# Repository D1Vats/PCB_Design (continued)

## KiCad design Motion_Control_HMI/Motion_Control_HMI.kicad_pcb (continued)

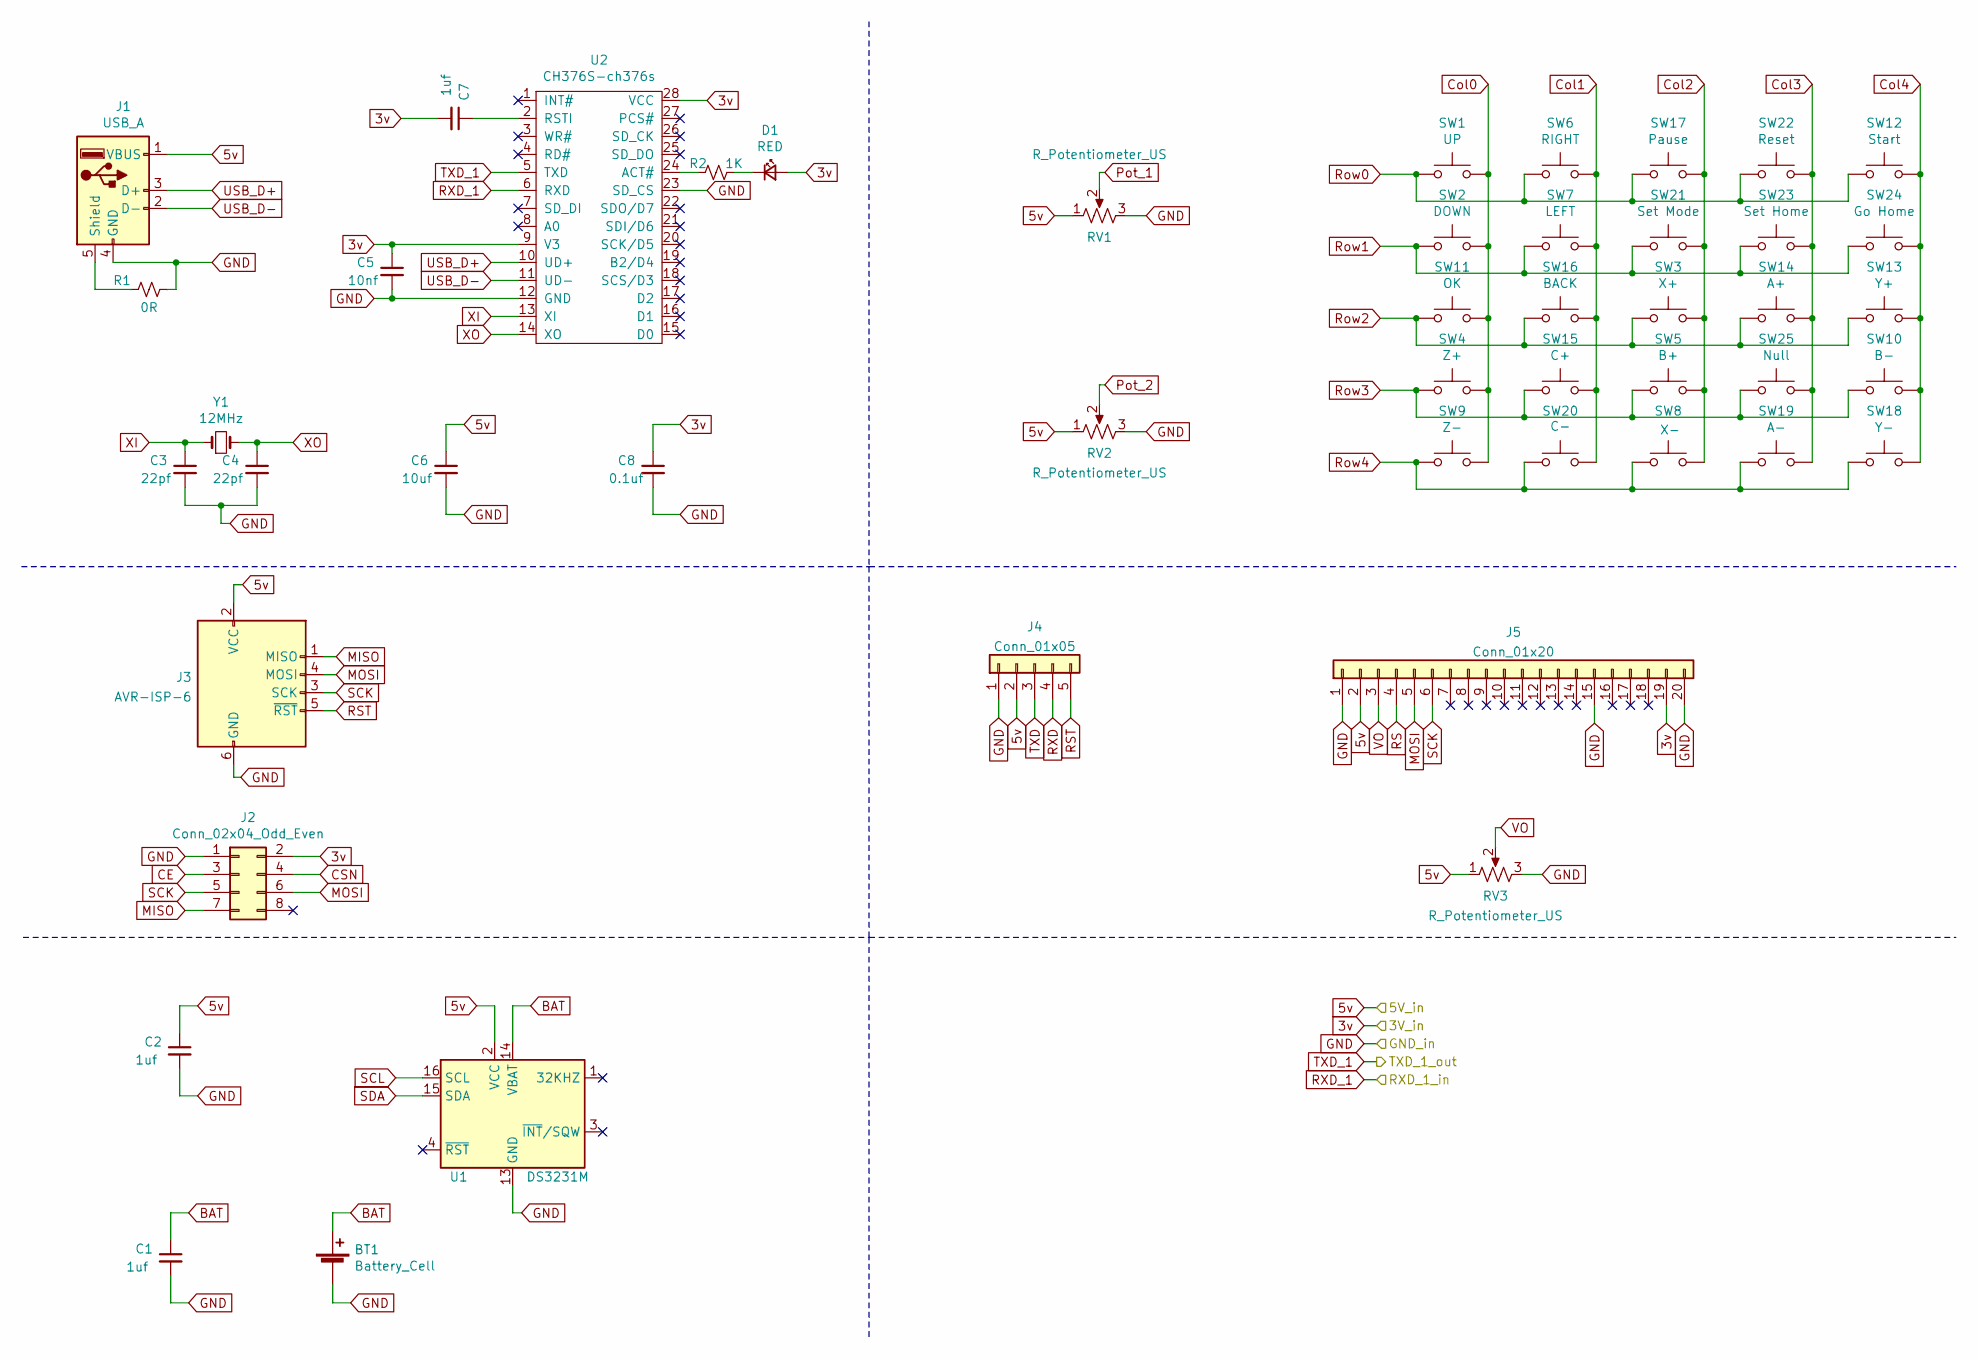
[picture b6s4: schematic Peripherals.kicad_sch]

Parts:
BT1: Battery_Cell; BatteryHolder_Keystone_104_1x23mm
C1, C2, C7: 1uf; C_0805_2012Metric
C3, C4: 22pf; C_0805_2012Metric
C5: 10nf; C_0805_2012Metric
C6: 10uf; C_0805_2012Metric
C8: 0.1uf; C_0805_2012Metric
D1: RED; LED_0805_2012Metric
J1: USB_A; USB_A_Molex_67643_Horizontal
J2: Conn_02x04_Odd_Even; PinSocket_2x04_P2.54mm_Vertical
J3: AVR-ISP-6; PinHeader_2x03_P2.54mm_Vertical
J4: Conn_01x05; PinHeader_1x05_P2.54mm_Vertical
J5: Conn_01x20; PinHeader_1x20_P2.54mm_Vertical
R1: 0R; R_0805_2012Metric
R2: 1K; R_0805_2012Metric
RV1, RV2: R_Potentiometer_US; JST_EH_B3B-EH-A_1x03_P2.50mm_Vertical
RV3: R_Potentiometer_US; Potentiometer_ACP_CA9-H3,8_Horizontal
SW1: UP; Key_Dome
SW2: DOWN; Key_Dome
SW3: X+; Key_Dome
SW4: Z+; Key_Dome
SW5: B+; Key_Dome
SW6: RIGHT; Key_Dome
SW7: LEFT; Key_Dome
SW8: X-; Key_Dome
SW9: Z-; Key_Dome
SW10: B-; Key_Dome
SW11: OK; Key_Dome
SW12: Start; Key_Dome
SW13: Y+; Key_Dome
SW14: A+; Key_Dome
SW15: C+; Key_Dome
SW16: BACK; Key_Dome
SW17: Pause; Key_Dome
SW18: Y-; Key_Dome
SW19: A-; Key_Dome
SW20: C-; Key_Dome
SW21: Set Mode; Key_Dome
SW22: Reset; Key_Dome
SW23: Set Home; Key_Dome
SW24: Go Home; Key_Dome
SW25: Null; Key_Dome
U1: DS3231M; SOIC-16W_7.5x10.3mm_P1.27mm
U2: CH376S-ch376s; SOIC-28W_7.5x17.9mm_P1.27mm
Y1: 12MHz; Crystal_HC49-4H_Vertical

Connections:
3.3V_OUT: C5.1, C7.2, C8.1, D1.2 (A), J2.2, J5.19, U2.9 (V3), U2.28 (VCC); also elsewhere on the board
5v: C2.1, C6.1, J1.1 (VBUS), J3.2 (VCC), J4.2, J5.2, RV1.1, RV2.1, RV3.1, U1.2 (VCC); also elsewhere on the board
BAT: BT1.1 (+), C1.1, U1.14 (VBAT)
CE: J2.3; also elsewhere on the board
CSN: J2.4; also elsewhere on the board
Col0: SW1.2, SW2.2, SW4.2, SW9.2, SW11.2; also elsewhere on the board
Col1: SW6.2, SW7.2, SW15.2, SW16.2, SW20.2; also elsewhere on the board
Col2: SW3.2, SW5.2, SW8.2, SW17.2, SW21.2; also elsewhere on the board
Col3: SW14.2, SW19.2, SW22.2, SW23.2, SW25.2; also elsewhere on the board
Col4: SW10.2, SW12.2, SW13.2, SW18.2, SW24.2; also elsewhere on the board
GND: BT1.2 (-), C1.2, C2.2, C3.2, C4.2, C5.2, C6.2, C8.2, J1.4 (GND), J2.1, J3.6 (GND), J4.1, J5.1, J5.15, J5.20, R1.1, RV1.3, RV2.3, RV3.3, U1.5 (GND), U1.6 (GND), U1.7 (GND), U1.8 (GND), U1.9 (GND), U1.10 (GND), U1.11 (GND), U1.12 (GND), U1.13 (GND), U2.12 (GND), U2.23 (SD_CS); also elsewhere on the board
LV_TXD_1: U2.6 (RXD); also elsewhere on the board
MISO: J2.7, J3.1 (MISO); also elsewhere on the board
MOSI: J2.6, J3.4 (MOSI), J5.5; also elsewhere on the board
unnamed: C7.1, U2.2 (RSTI)
unnamed: D1.1 (K), R2.1
unnamed: J1.5 (Shield), R1.2
unnamed: R2.2, U2.24 (ACT#)
Pot_1: RV1.2; also elsewhere on the board
Pot_2: RV2.2; also elsewhere on the board
RS: J5.4; also elsewhere on the board
RST: J3.5 (~RST), J4.5; also elsewhere on the board
RXD: J4.4; also elsewhere on the board
Row0: SW1.1, SW6.1, SW12.1, SW17.1, SW22.1; also elsewhere on the board
Row1: SW2.1, SW7.1, SW21.1, SW23.1, SW24.1; also elsewhere on the board
Row2: SW3.1, SW11.1, SW13.1, SW14.1, SW16.1; also elsewhere on the board
Row3: SW4.1, SW5.1, SW10.1, SW15.1, SW25.1; also elsewhere on the board
Row4: SW8.1, SW9.1, SW18.1, SW19.1, SW20.1; also elsewhere on the board
SCK: J2.5, J3.3 (SCK), J5.6; also elsewhere on the board
SCL: U1.16 (SCL); also elsewhere on the board
SDA: U1.15 (SDA); also elsewhere on the board
TXD: J4.3; also elsewhere on the board
TXD_1: U2.5 (TXD); also elsewhere on the board
USB_D+: J1.3 (D+), U2.10 (UD+)
USB_D-: J1.2 (D-), U2.11 (UD-)
VO: J5.3, RV3.2
XI: C3.1, U2.13 (XI), Y1.1
XO: C4.1, U2.14 (XO), Y1.2

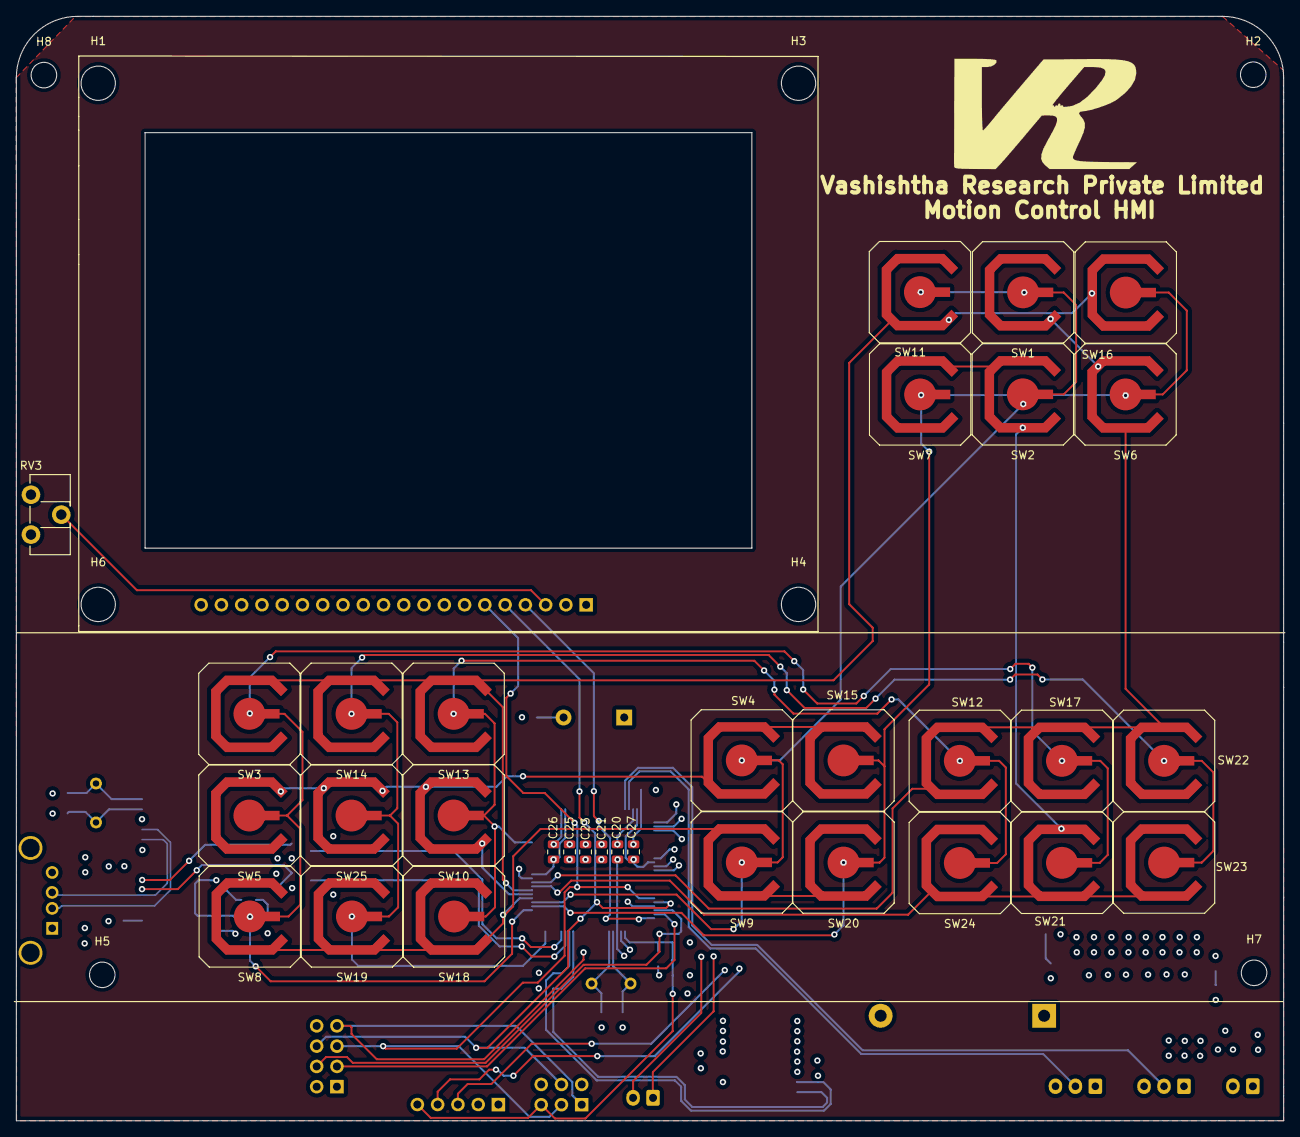
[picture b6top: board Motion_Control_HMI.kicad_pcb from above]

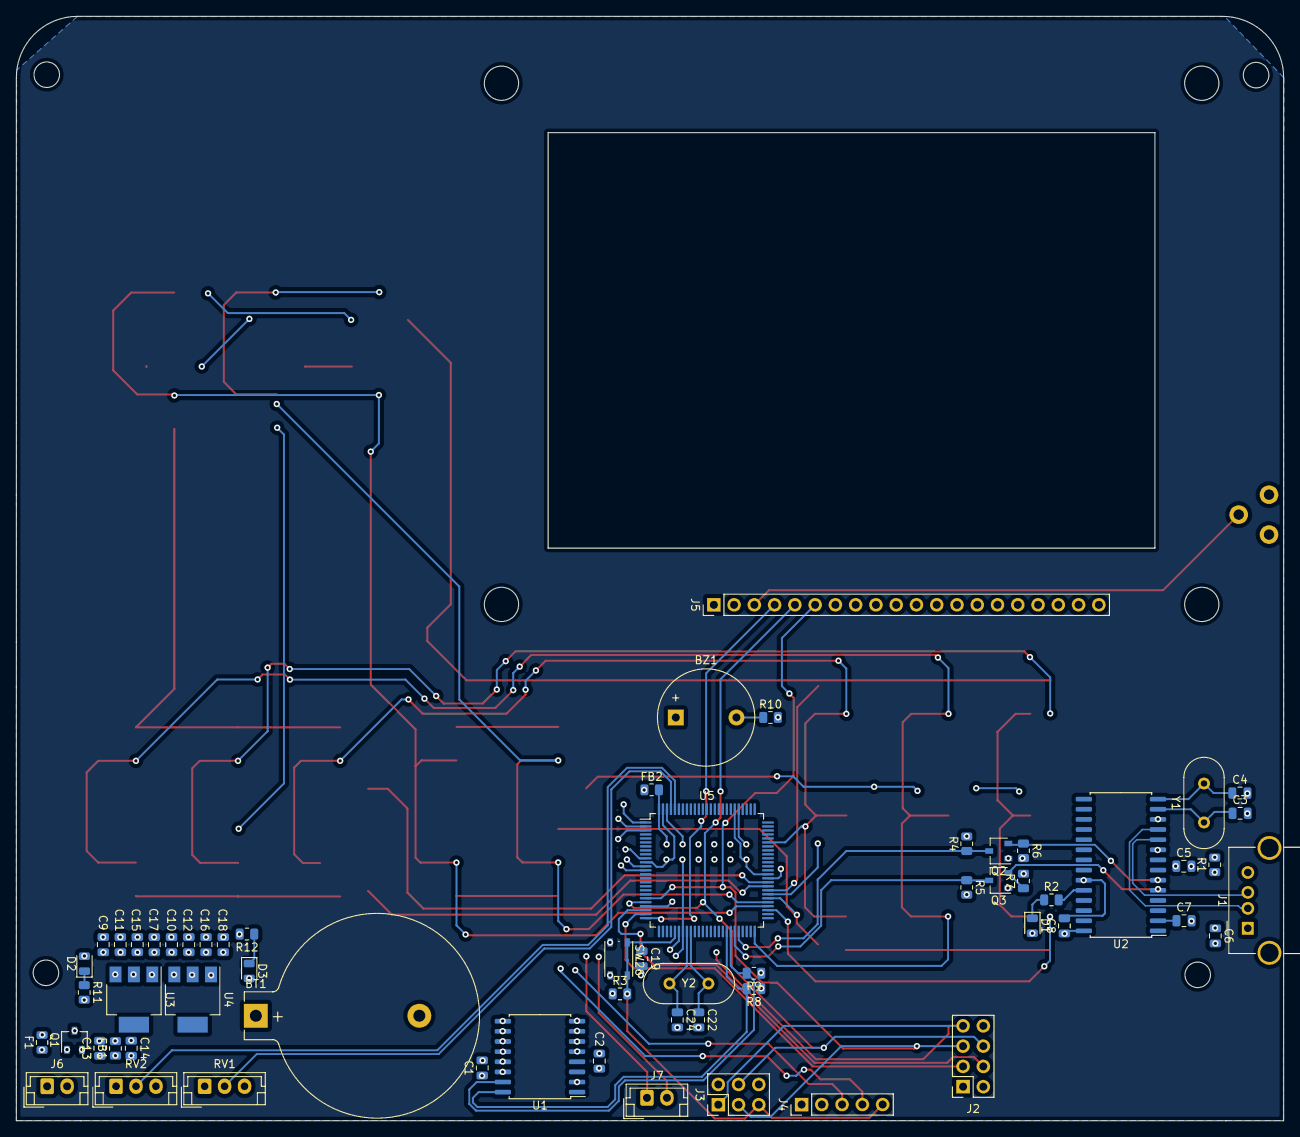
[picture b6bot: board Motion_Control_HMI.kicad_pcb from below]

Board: 4 copper layers, 158.9 x 138.4 mm, 101 parts (61 on the bottom side), 54 nets.

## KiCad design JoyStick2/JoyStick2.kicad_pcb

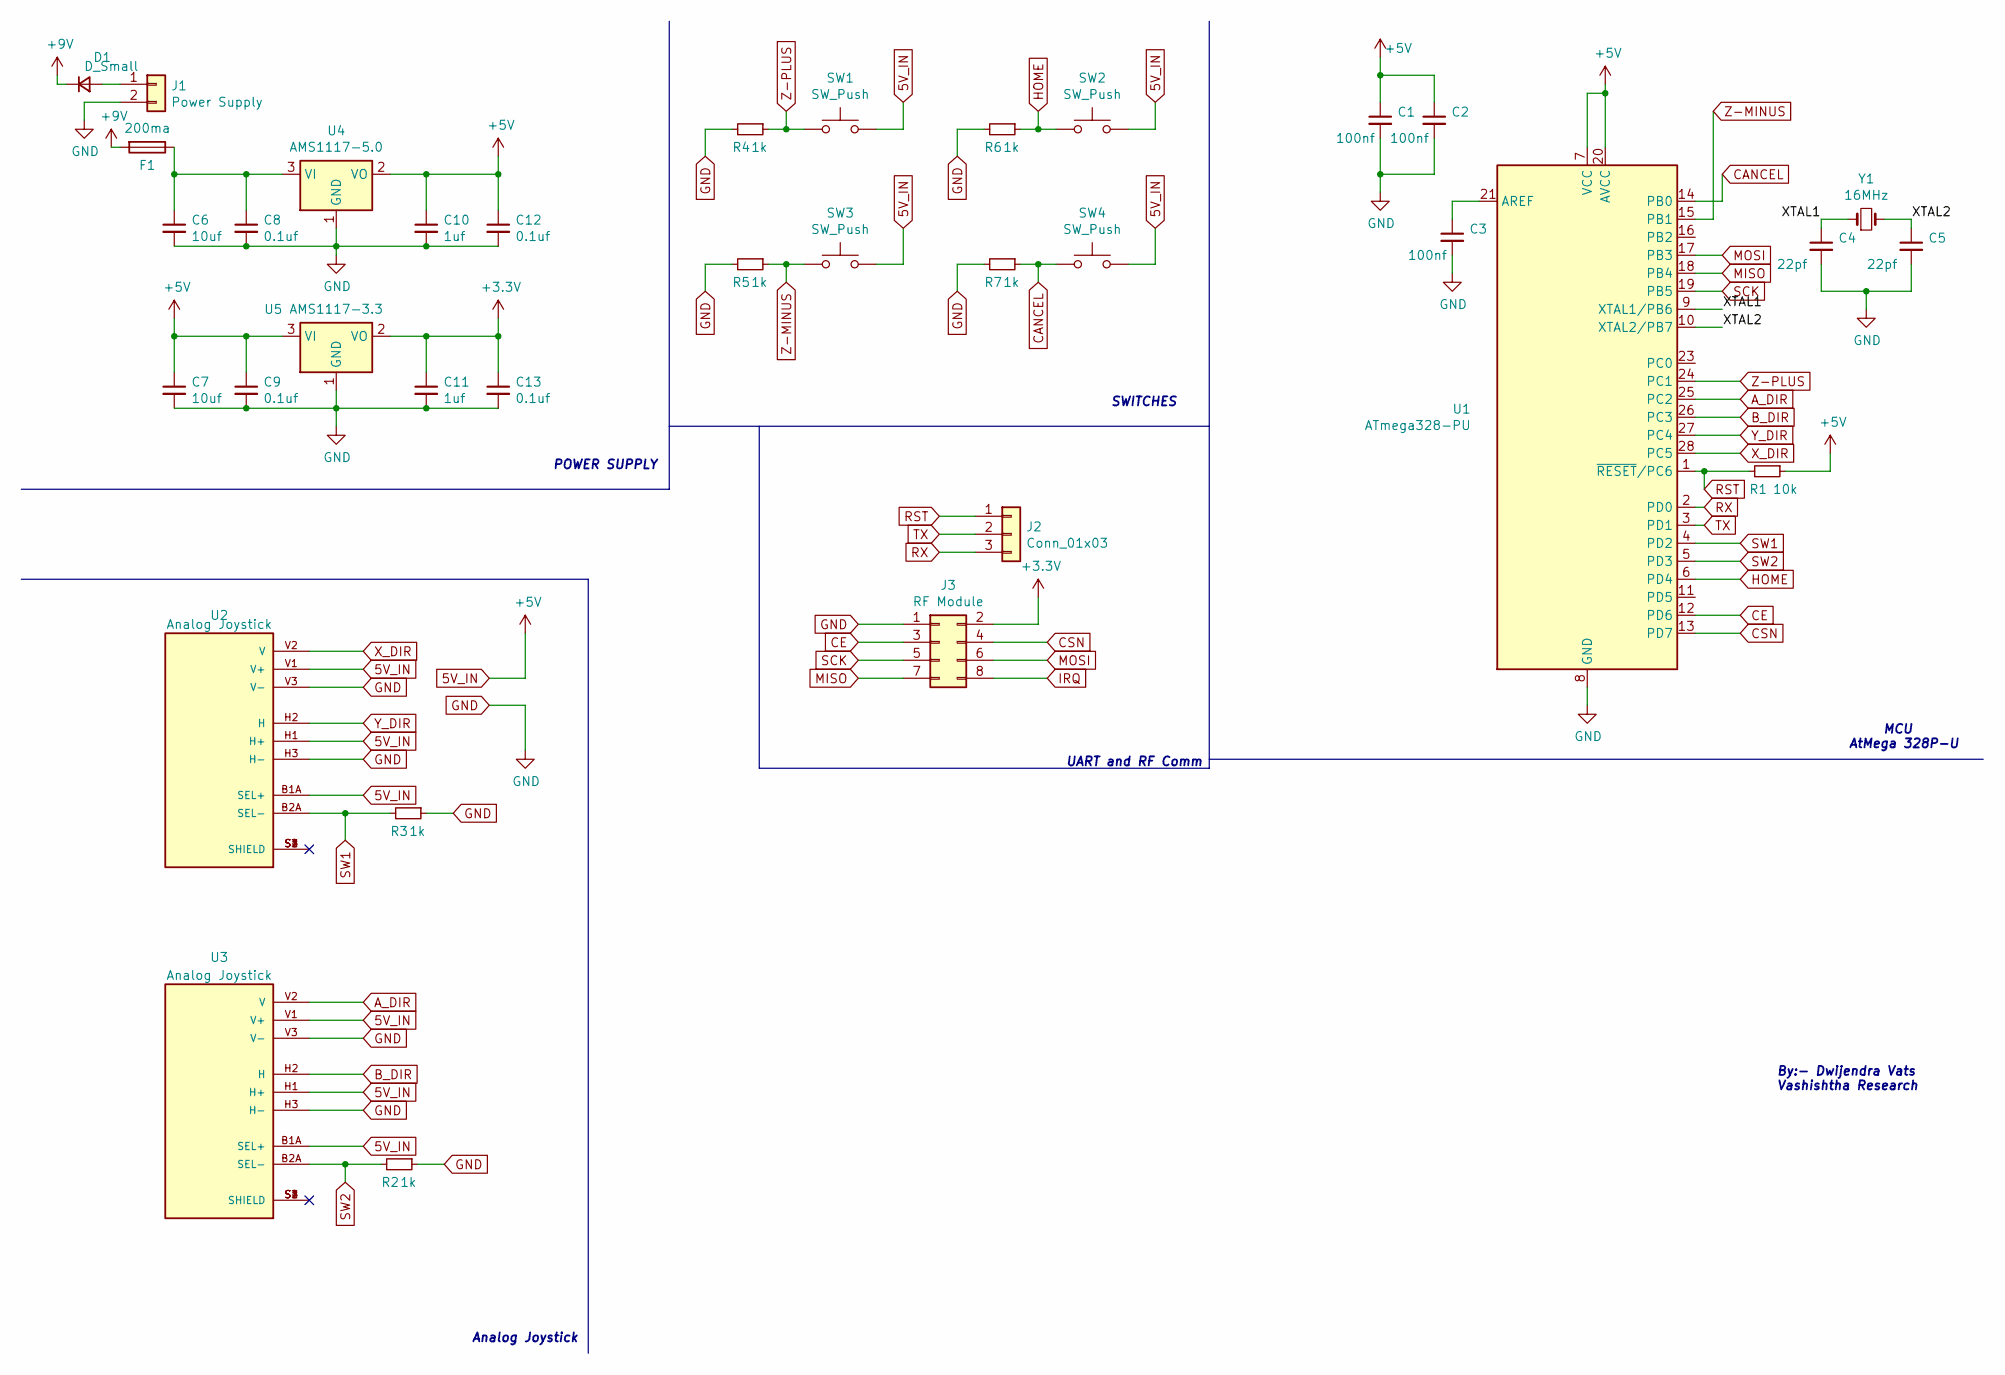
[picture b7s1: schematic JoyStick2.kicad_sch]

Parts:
C1, C2, C3: 100nf; C_0603_1608Metric
C4, C5: 22pf; C_0603_1608Metric
C6, C7: 10uf; C_0805_2012Metric
C8, C9, C12, C13: 0.1uf; C_0603_1608Metric
C10, C11: 1uf; C_0805_2012Metric
D1: D_Small; D_DO-41_SOD81_P10.16mm_Horizontal
F1: 200ma
J1: Power Supply; PinSocket_1x02_P2.54mm_Vertical
J2: Conn_01x03; PinSocket_1x03_P2.54mm_Vertical
J3: RF Module; PinHeader_2x04_P2.54mm_Vertical
R1: 10k; R_0805_2012Metric
R2, R3, R4, R5, R6, R7: 1k; R_0805_2012Metric
SW1, SW2, SW3, SW4: SW_Push; SW_PUSH_6mm_H13mm
U1: ATmega328-PU; DIP-28_W7.62mm
U2, U3: Analog Joystick; XDCR_COM-09032; PARTREV N/A
U4: AMS1117-5.0; SOT-223-3_TabPin2
U5: AMS1117-3.3; SOT-223-3_TabPin2
Y1: 16MHz; Crystal_HC49-4H_Vertical

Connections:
5V_IN: C1.1, C2.1, C7.1, C9.1, C10.1, C12.1, R1.1, SW1.2, SW2.2, SW3.2, SW4.2, U1.7 (VCC), U1.20 (AVCC), U2.B1A (SEL+), U2.H1 (H+), U2.V1 (V+), U3.B1A (SEL+), U3.H1 (H+), U3.V1 (V+), U4.2 (VO), U5.3 (VI); also elsewhere on the board
+3V3: C11.1, C13.1, J3.2, U5.2 (VO); also elsewhere on the board
/XTAL1: C4.1, U1.9 (XTAL1/PB6), Y1.1
/XTAL2: C5.1, U1.10 (XTAL2/PB7), Y1.2
A_DIR: U1.25 (PC2), U3.V2 (V)
B_DIR: U1.26 (PC3), U3.H2 (H)
CANCEL: R7.1, SW4.1, U1.14 (PB0)
CE: J3.3, U1.12 (PD6)
CSN: J3.4, U1.13 (PD7)
GND: C1.2, C2.2, C3.2, C4.2, C5.2, C6.2, C7.2, C8.2, C9.2, C10.2, C11.2, C12.2, C13.2, J1.2, J3.1, R2.1, R3.1, R4.2, R5.2, R6.2, R7.2, U1.8 (GND), U1.22 (GND), U2.H3 (H-), U2.V3 (V-), U3.H3 (H-), U3.V3 (V-), U4.1 (GND), U5.1 (GND); also elsewhere on the board
HOME: R6.1, SW2.1, U1.6 (PD4)
IRQ: J3.8, U1.11 (PD5)
MISO: J3.7, U1.18 (PB4)
MOSI: J3.6, U1.17 (PB3)
unnamed: C3.1, U1.21 (AREF)
unnamed: D1.2 (A), J1.1
unnamed: U2.S1 (SHIELD), U2.S2 (SHIELD), U2.S3 (SHIELD), U2.S4 (SHIELD)
unnamed: U3.S1 (SHIELD), U3.S2 (SHIELD), U3.S3 (SHIELD), U3.S4 (SHIELD)
RST: J2.1, R1.2, U1.1 (~RESET/PC6)
RX: J2.3, U1.2 (PD0)
SCK: J3.5, U1.19 (PB5)
SW1: R3.2, U1.4 (PD2), U2.B2A (SEL-)
SW2: R2.2, U1.5 (PD3), U3.B2A (SEL-)
TX: J2.2, U1.3 (PD1)
X_DIR: U1.28 (PC5), U2.V2 (V)
Y_DIR: U1.27 (PC4), U2.H2 (H)
Z-MINUS: R5.1, SW3.1, U1.15 (PB1)
Z-PLUS: R4.1, SW1.1, U1.24 (PC1)

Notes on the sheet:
Analog Joystick
UART and RF Comm
POWER SUPPLY
By:- Dwijendra Vats Vashishtha Research
MCU AtMega 328P-U
SWITCHES

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
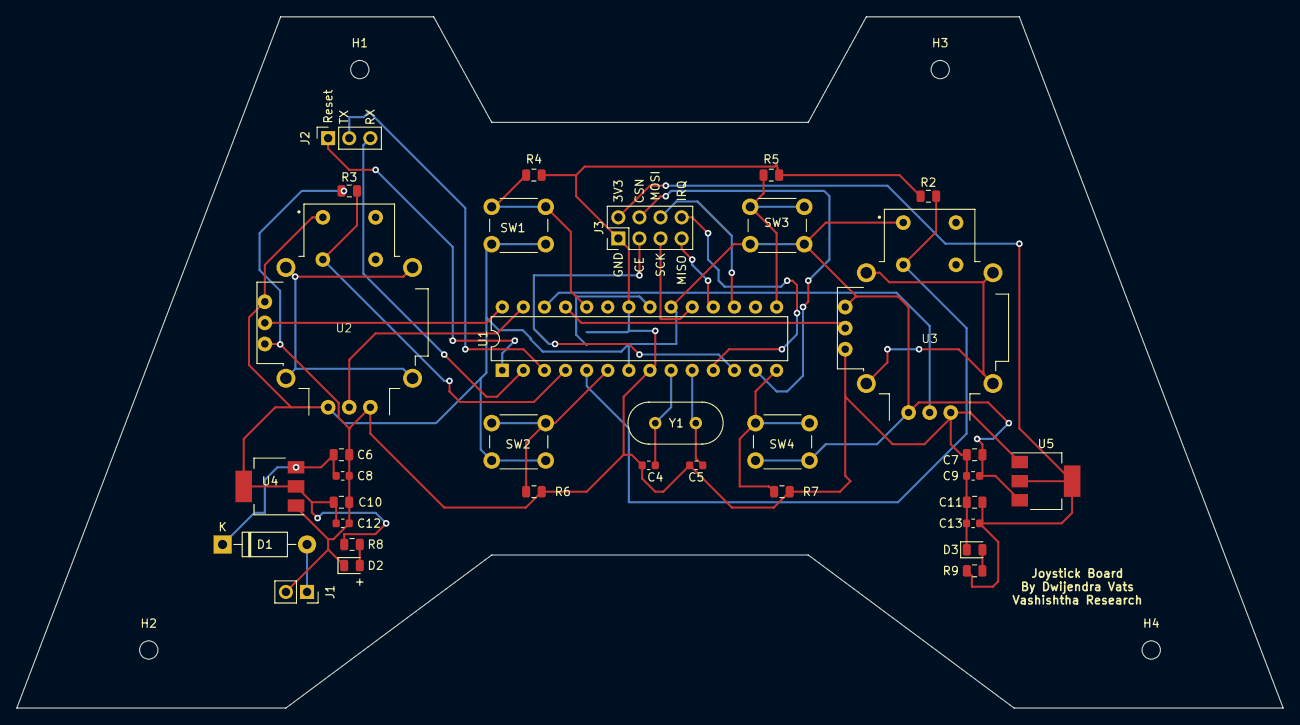
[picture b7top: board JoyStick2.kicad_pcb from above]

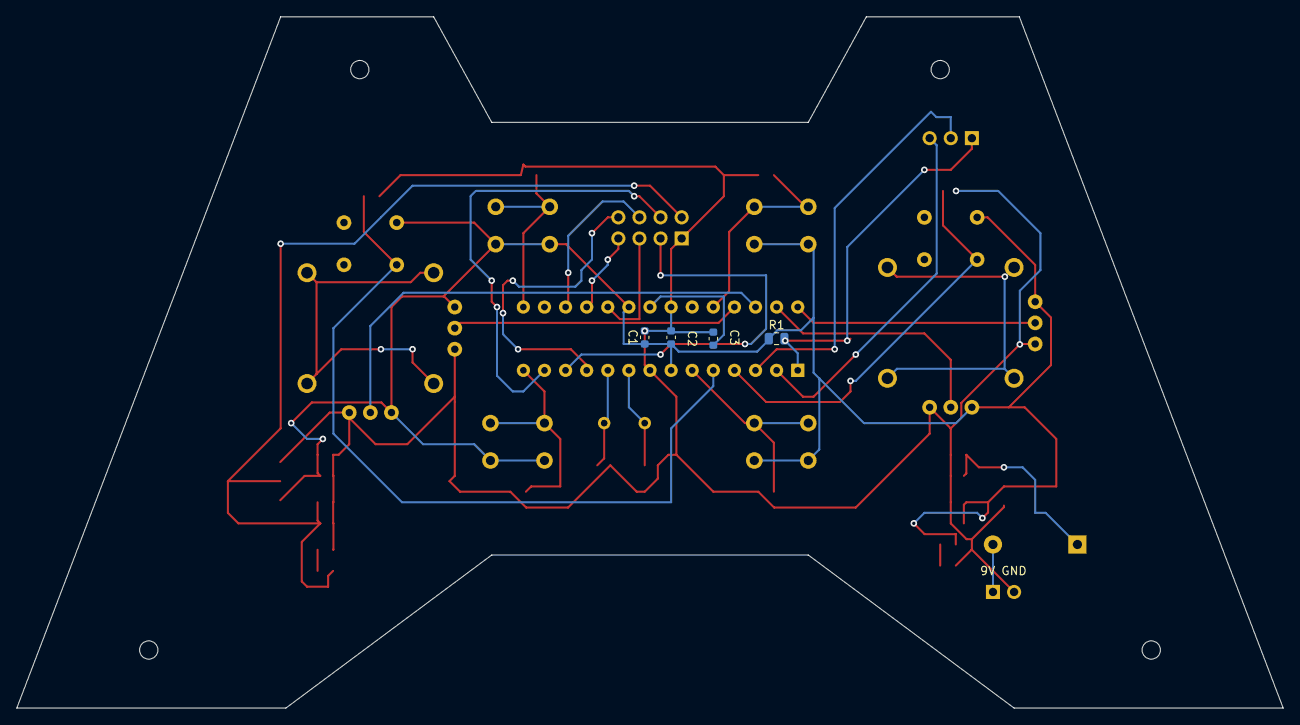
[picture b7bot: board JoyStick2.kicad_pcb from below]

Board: 2 copper layers, 152.4 x 83.2 mm, 42 parts (4 on the bottom side), 31 nets.

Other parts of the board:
D2, D3: LED; LED_0805_2012Metric
H1, H2, H3, H4: MountingHole; MountingHole_2.2mm_M2
R8, R9: 1k; R_0805_2012Metric

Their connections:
5V_IN: R8.1; also elsewhere on the board
+3V3: R9.1; also elsewhere on the board
GND: D2.1, D3.1; also elsewhere on the board
unnamed: D2.2, R8.2
unnamed: D3.2, R9.2

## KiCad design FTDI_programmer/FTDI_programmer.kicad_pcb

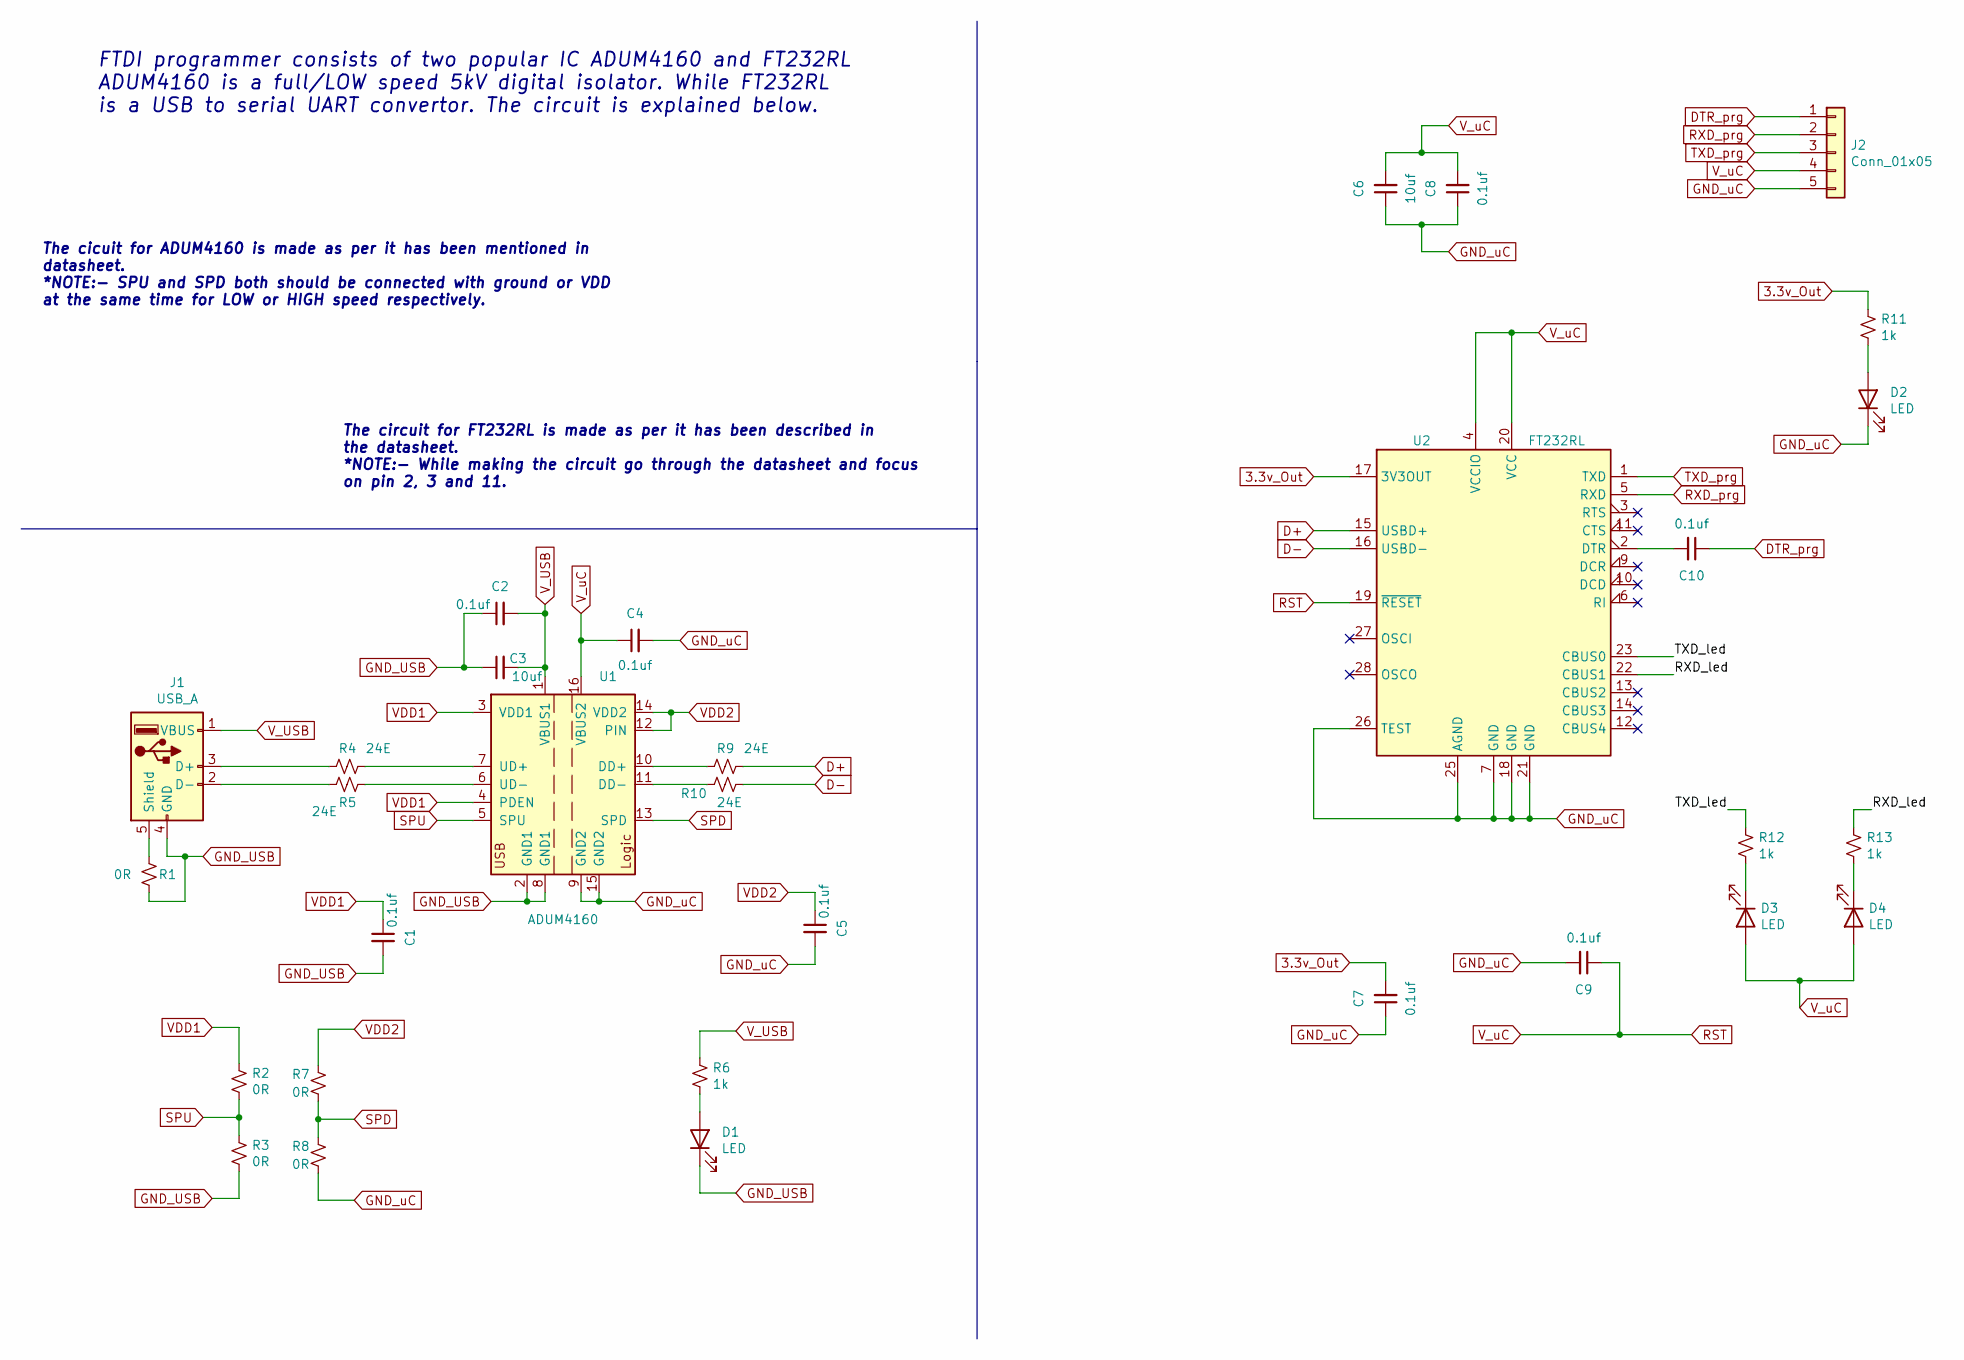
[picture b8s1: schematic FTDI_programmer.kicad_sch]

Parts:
C1, C2, C4, C5, C7, C8, C9, C10: 0.1uf; C_0805_2012Metric
C3, C6: 10uf; C_0805_2012Metric
D1, D2, D3, D4: LED; LED_0805_2012Metric
J1: USB_A; USB_A_Molex_67643_Horizontal
J2: Conn_01x05; PinHeader_1x05_P2.54mm_Vertical
R1, R2, R3, R7, R8: 0R; R_0805_2012Metric
R4, R5, R9, R10: 24E; R_0805_2012Metric
R6, R11, R12, R13: 1k; R_0805_2012Metric
U1: ADUM4160; SOIC-16W_7.5x10.3mm_P1.27mm
U2: FT232RL; SSOP-28_5.3x10.2mm_P0.65mm

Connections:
3.3v_Out: C7.2, R11.1, U2.17 (3V3OUT)
/RXD_led: R13.1, U2.22 (CBUS1)
/TXD_led: R12.1, U2.23 (CBUS0)
D+: R9.1, U2.15 (USBD+)
D-: R10.1, U2.16 (USBD-)
DTR_prg: C10.1, J2.1
GND_USB: C1.2, C2.1, C3.1, D1.1 (K), J1.4 (GND), R1.2, R3.2, U1.2 (GND1), U1.8 (GND1)
GND_uC: C4.2, C5.2, C6.1, C7.1, C8.1, C9.2, D2.1 (K), J2.5, R8.2, U1.9 (GND2), U1.15 (GND2), U2.7 (GND), U2.18 (GND), U2.21 (GND), U2.25 (AGND), U2.26 (TEST)
unnamed: C10.2, U2.2 (DTR)
unnamed: D1.2 (A), R6.2
unnamed: D2.2 (A), R11.2
unnamed: D3.1 (K), R12.2
unnamed: D4.1 (K), R13.2
unnamed: J1.2 (D-), R5.2
unnamed: J1.3 (D+), R4.2
unnamed: J1.5 (Shield), R1.1
unnamed: R4.1, U1.7 (UD+)
unnamed: R5.1, U1.6 (UD-)
unnamed: R9.2, U1.10 (DD+)
unnamed: R10.2, U1.11 (DD-)
RST: C4.1, C6.2, C8.2, C9.1, D3.2 (A), D4.2 (A), J2.4, U1.16 (VBUS2), U2.4 (VCCIO), U2.19 (~RESET), U2.20 (VCC)
RXD_prg: J2.2, U2.5 (RXD)
SPD: R7.2, R8.1, U1.13 (SPD)
SPU: R2.2, R3.1, U1.5 (SPU)
TXD_prg: J2.3, U2.1 (TXD)
VDD1: C1.1, R2.1, U1.3 (VDD1), U1.4 (PDEN)
VDD2: C5.1, R7.1, U1.12 (PIN), U1.14 (VDD2)
V_USB: C2.2, C3.2, J1.1 (VBUS), R6.1, U1.1 (VBUS1)

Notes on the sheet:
FTDI programmer consists of two popular IC ADUM4160 and FT232RL ADUM4160 is a full/LOW speed 5kV digital isolator. While FT232RL is a USB to serial UART convertor. The circuit is explained below.
The cicuit for ADUM4160 is made as per it has been mentioned in datasheet. *NOTE:- SPU and SPD both should be connected with ground or VDD at the same time for LOW or HIGH speed respectively.
The circuit for FT232RL is made as per it has been described in the datasheet. *NOTE:- While making the circuit go through the datasheet and focus on pin 2, 3 and 11.

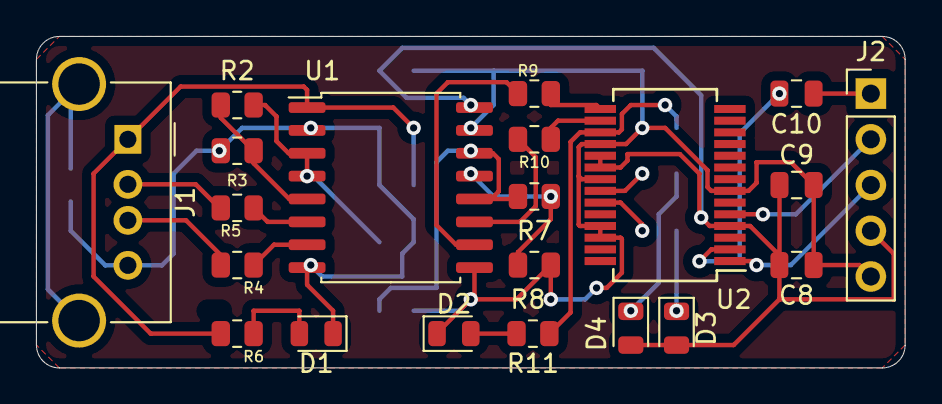
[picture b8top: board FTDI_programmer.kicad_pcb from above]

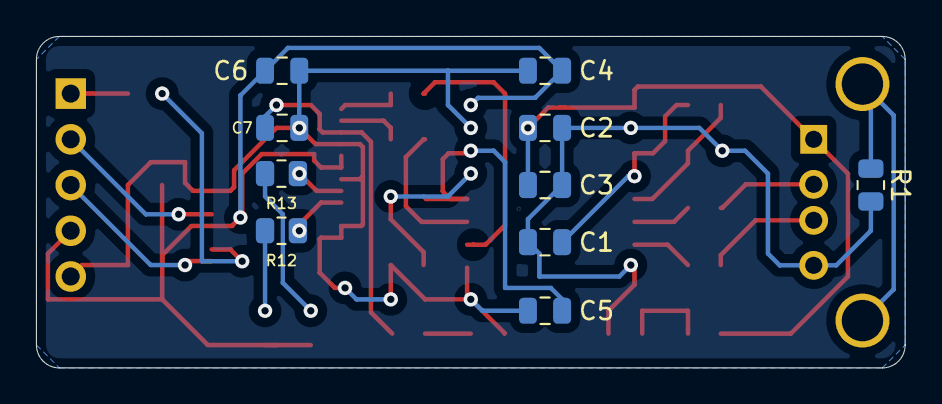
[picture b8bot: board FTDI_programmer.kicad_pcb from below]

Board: 2 copper layers, 48.3 x 18.4 mm, 31 parts (10 on the bottom side), 28 nets.
